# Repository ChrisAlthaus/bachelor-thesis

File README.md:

# Ambient Notifications for a Shape-Changing Display

## Abstract 

This thesis is about a shape-changing display, which can display information through height adjustment and led lights. An existing system was used to control the shape-changing display. This system will be examined and then redesigned with the objective to make it simpler and more compact, so that a user can take it with home. The developed system should allow visualization of real-time infor-mation from web sources. Furthermore, it should display information in an unob-trusive manner.
The displayed scenarios, for example the current or predicted temperature, can be configured in a graphical user interface. It can be specified, how the information will be displayed. This, among others, includes specification of the led colors or different visualization modes. Therefore, a concept for displaying quantitative val-ues is developed. Different animations were implemented to provide better feed-back of the developed system and scenarios.

**Links to Written Thesis & Presentation**

Written thesis: https://www.dropbox.com/s/n5zsrz6mi4d3moz/Ambient%20Notifications%20For%20A%20Shape%20Changing%20Display.pdf?dl=0 <br />
Presentation: https://www.dropbox.com/s/1c8k933pfb60718/Final%20presentation.pdf?dl=0

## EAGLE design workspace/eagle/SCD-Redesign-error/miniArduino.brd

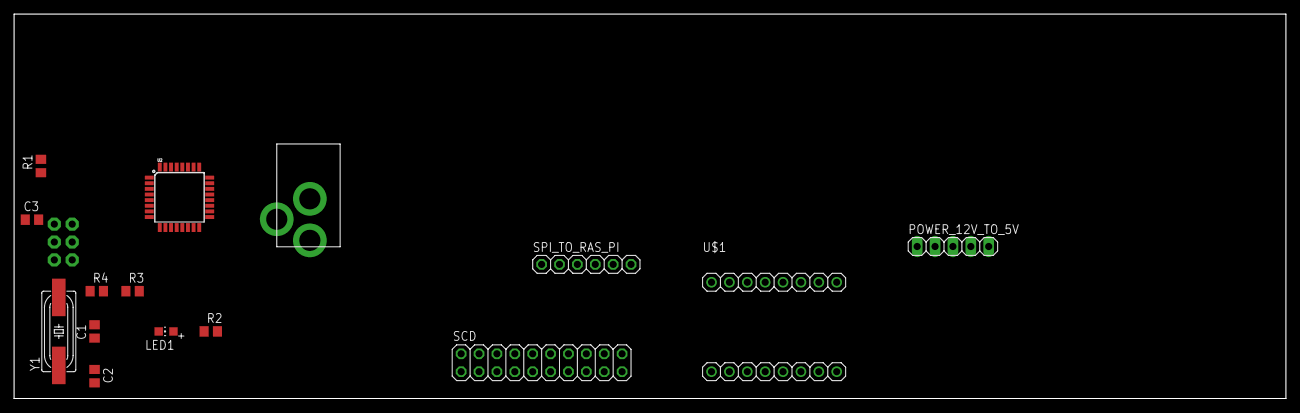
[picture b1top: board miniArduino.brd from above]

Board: 2 copper layers, 180.6 x 54.6 mm, 16 parts (1 on the bottom side), 22 nets, no tracks yet.

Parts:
C1, C2: 22p; C0805
C3: 100n; C0805
J1: AVR_SPI_PRG_6PTH; 2X3
LED1: CHIP-LED0805
POWER_12V: 2.1MMJACKTHM; PJ-102A
POWER_12V_TO_5V: 1X05
R1: 10k; R0805
R2: 1k; R0805
R3: 4,7k; R0805
R4: 2,2k; R0805
SCD: 2X10
SPI_TO_RAS_PI: 1X06
U2: ATMEGA328P_TQFP; TQFP32-08
U$1: A4998_BREAKOUT; A4988_BREAKOUT
Y1: HC49UP

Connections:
GND: C1.1, C2.1, C3.1, J1.6, LED1.C, POWER_12V.RING, POWER_12V.RING_SW, R3.1, SCD.2, SCD.4, SCD.6, U2.3, U2.5, U2.21, U$1.12
unnamed: R3.2, R4.2, U2.16
unnamed: J1.3, R2.2, U2.17
unnamed: J1.4, U2.15
unnamed: SCD.8, U2.24
unnamed: U2.1, U2.9, U$1.15
unnamed: LED1.A, R2.1
unnamed: J1.5, R1.2, U2.29, U$1.2
unnamed: C1.2, U2.7, Y1.2
unnamed: C2.2, U2.8, Y1.1
unnamed: U2.13, U$1.9
unnamed: U2.2, U$1.10
unnamed: U$1.13, U$1.14
unnamed: U2.28, U$1.16
unnamed: J1.1, R4.1
unnamed: C3.2, J1.2, R1.1, SCD.1, SCD.3, SCD.5, U2.4, U2.6, U2.18, U2.20
unnamed: SCD.10, SCD.12, U2.25, U2.26
unnamed: SCD.14, U$1.3
unnamed: SCD.16, U$1.4
unnamed: SCD.20, U$1.5
unnamed: SCD.18, U$1.6
unnamed: SCD.7, U2.12

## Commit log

2017-10-05 Zeitplan hinzugefügt
2017-10-12 bachelor-thesis doc added
2017-10-12 image of old setup
2017-10-12 previous_setup png added
2017-12-01 added eagle files
2017-12-01 Add workspace files
2017-12-12 eagle files uploaded
2017-12-12 deleted files
2018-01-06 uploaded files
2018-01-21 updated bachelor thesis
2018-01-23 update workspace folder
2018-01-29 MovingBarGui uploaded
2018-01-30 source code and libraries upload
2018-01-30 uploaded model files
2018-01-30 updated thesis
2018-02-02 uploaded thesis
2018-02-05 finished files

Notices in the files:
parts and their libraries:
SparkFun-DigitalIC: Licensing: Creative Commons ShareAlike 4.0 International - https://creativecommons.org/licenses/by-sa/4.0
